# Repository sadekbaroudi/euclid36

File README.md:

# Support me!

I have spent a lot of time and money designing prototypes, testing, developing, etc. Any contributions would be greatly appreciated!

If you don't want to, or can't afford to support me, please send me a message to let me know you've built one, along with pictures. Also, feel free to submit a pull request with pictures into this repository. I'd be happy to showcase your build.

Reddit: /u/sadekbaroudi
Discord: sadekbaroudi#1258

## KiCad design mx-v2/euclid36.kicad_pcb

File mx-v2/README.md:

# euclid36

## The euclid36 supports the following:
* 36 keys
* Two rotary encoders
* 10 bottom facing LEDs for underglow
* 3 top facing LEDs for illumination in the center of the board
* Horizontal OLED near the top of the board
* 3 different types of Joysticks for mouse control
	* PS2/PS3/PS4 type joystick with click button (center of the board)
		* https://www.adafruit.com/product/512
	* 2 axis thumbstick
		* https://www.adafruit.com/product/2765
	* PSP type thumbstick
		* https://www.adafruit.com/product/444
	
### Placement of features:

### Print this file to test the layout. It is to scale

### 3d render

### Layout

_At the time of creation, using Kicad 5.1.9 - This may not work with future versions_

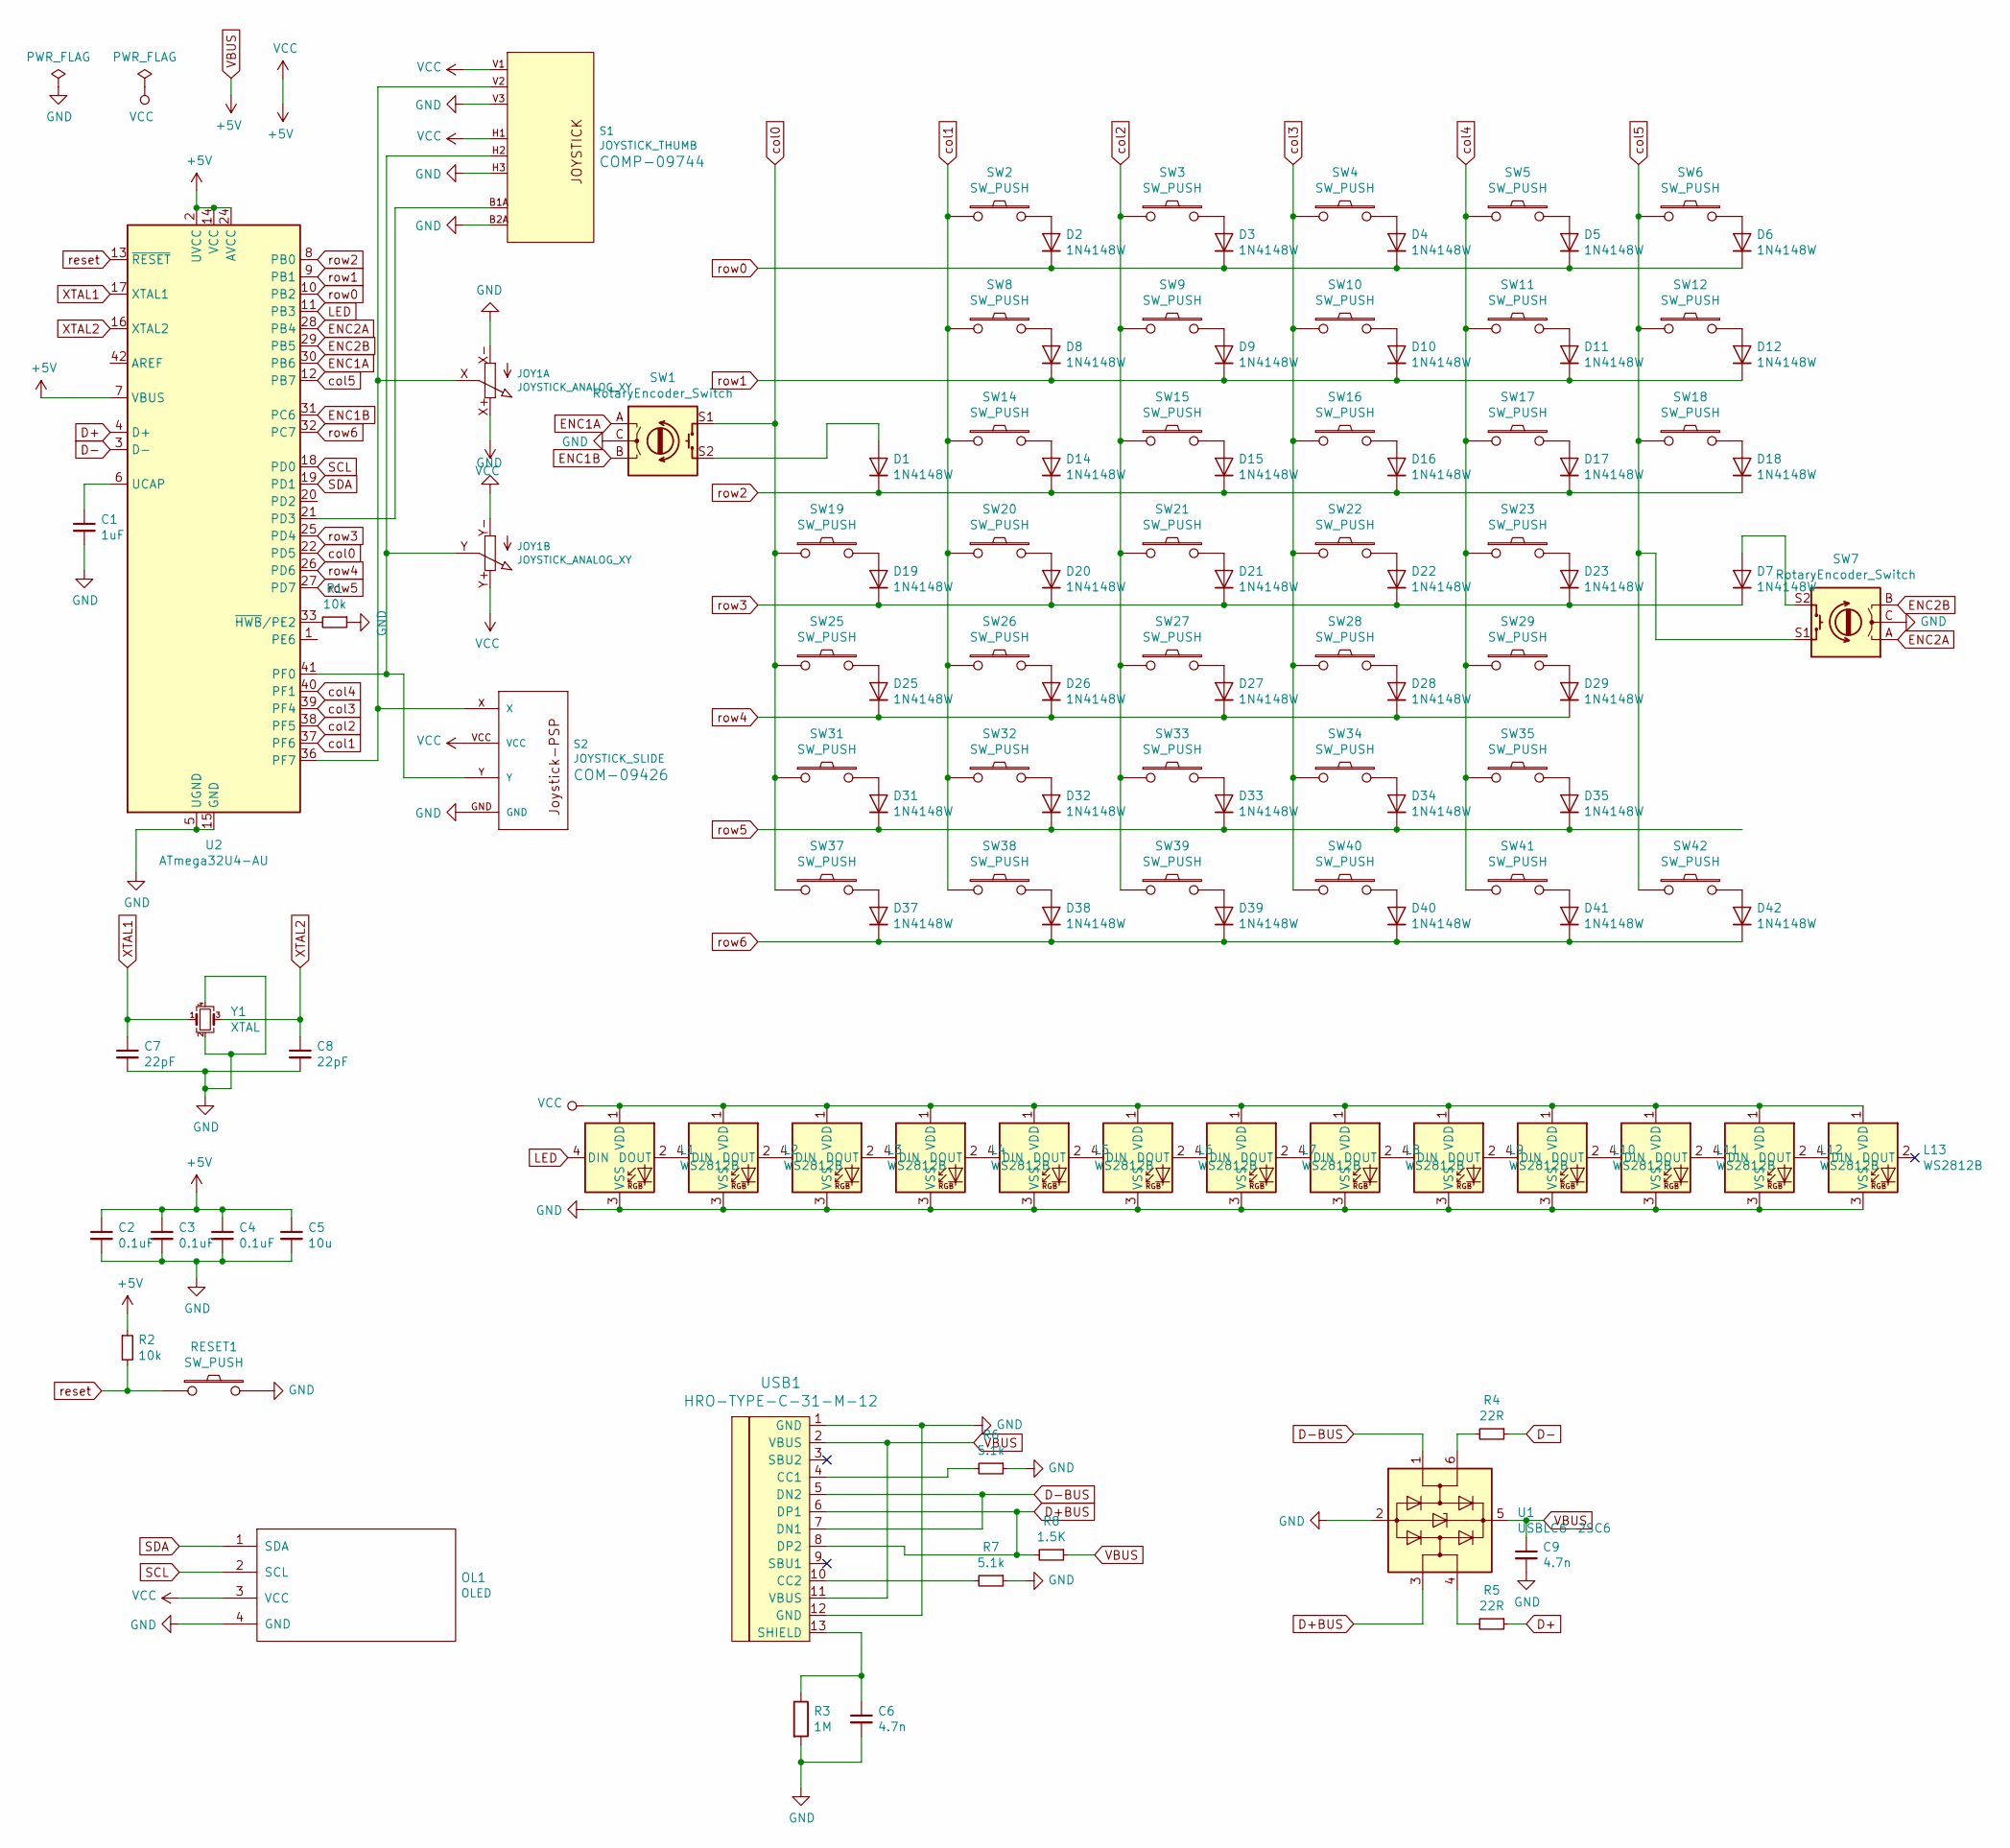
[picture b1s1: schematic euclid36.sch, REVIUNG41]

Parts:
C1: 1uF; C_0805_2012Metric_Pad1.18x1.45mm_HandSolder; LCSC C28323
C2, C3, C4: 0.1uF; C_0805_2012Metric_Pad1.18x1.45mm_HandSolder; LCSC C49678
C5: 10u; C_0805_2012Metric_Pad1.18x1.45mm_HandSolder; LCSC C15850
C6: 4.7n; C_0805_2012Metric; LCSC C50131
C7, C8: 22pF; C_0805_2012Metric_Pad1.18x1.45mm_HandSolder; LCSC C1804
C9: 4.7n; C_0805_2012Metric; LCSC C1744
D1, D2, D3, D4, D5, D6, D7, D8, D9, D10, D11, D12, D14, D15, D16, D17, D18, D19, D20, D21, D22, D23, D26, D27, D28, D29, D31, D32, D33, D34, D35, D37, D38, D39, D40, D41, D42: 1N4148W; D_SOD-123; LCSC C727110
D25: 1N4148W; D_SOD-123; LCSC C81598
JOY1: JOYSTICK_ANALOG_XY; JOYSTICK_ANALOG_MINITHM
L1, L2, L3, L4, L5, L6, L7, L8, L9, L10, L11, L12, L13: WS2812B; LED_WS2812B_PLCC4_5.0x5.0mm_P3.2mm; LCSC C114586
OL1: OLED; OLED_v2
R1, R2: 10k; R_0805_2012Metric; LCSC C17414
R3: 1M; R_0805_2012Metric; LCSC C17514
R4, R5: 22R; R_0805_2012Metric; LCSC C17561
R6, R7: 5.1k; R_0805_2012Metric; LCSC C27834
R8: 1.5K; R_0805_2012Metric; LCSC C4310
RESET1: SW_PUSH; ResetSW_1side
S1: JOYSTICK_THUMB; JOYSTICK
S2: JOYSTICK_SLIDE; JOYSTICK-PSP1000
SW1, SW7: RotaryEncoder_Switch; RotaryEncoder_EC11; LCSC C470750
SW2, SW3, SW4, SW5, SW6, SW8, SW9, SW10, SW11, SW12, SW14, SW15, SW16, SW17, SW18, SW19, SW20, SW21, SW22, SW23, SW25, SW26, SW27, SW28, SW29, SW31, SW32, SW33, SW34, SW35, SW37, SW38, SW39, SW40, SW41, SW42: SW_PUSH; MXOnly-1U-Hotswap
U1: USBLC6-2SC6; SOT-23-6; LCSC C558442
U2: ATmega32U4-AU; ATMEGA32U4-AU; LCSC C44854
USB1: HRO-TYPE-C-31-M-12; HRO-TYPE-C-31-M-12-Assembly; LCSC C165948
Y1: XTAL; Crystal_SMD_3225-4Pin_3.2x2.5mm; LCSC C13738

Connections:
D+: R5.1, U2.4 (D+)
D+BUS: R8.2, U1.3 (I/O2), USB1.6 (DP1), USB1.8 (DP2)
D-: R4.1, U2.3 (D-)
D-BUS: U1.1 (I/O1), USB1.5 (DN2), USB1.7 (DN1)
ENC1A: SW1.A, U2.30 (PB6)
ENC1B: SW1.B, U2.31 (PC6)
ENC2A: SW7.A, U2.28 (PB4)
ENC2B: SW7.B, U2.29 (PB5)
GND: C1.2, C2.2, C3.2, C4.2, C5.2, C6.2, C7.2, C8.2, C9.2, JOY1.X- (A), JOY1.Y- (A), L1.3 (VSS), L2.3 (VSS), L3.3 (VSS), L4.3 (VSS), L5.3 (VSS), L6.3 (VSS), L7.3 (VSS), L8.3 (VSS), L9.3 (VSS), L10.3 (VSS), L11.3 (VSS), L12.3 (VSS), L13.3 (VSS), OL1.4 (GND), R1.1, R3.2, R6.1, R7.1, RESET1.2, S1.B2A (SEL-), S1.H3 (H-), S1.V3 (V-), S2.GND, SW1.C, SW7.C, U1.2 (GND), U2.5 (UGND), U2.15 (GND), U2.23 (GND), U2.35 (GND), U2.43 (GND), USB1.1 (GND), USB1.12 (GND), Y1.2, Y1.4
LED: L1.4 (DIN), U2.11 (PB3)
unnamed: C1.1, U2.6 (UCAP)
unnamed: C6.1, R3.1, USB1.13 (SHIELD)
unnamed: D1.2 (A), SW1.S2
unnamed: D2.2 (A), SW2.2
unnamed: D3.2 (A), SW3.2
unnamed: D4.2 (A), SW4.2
unnamed: D5.2 (A), SW5.2
unnamed: D6.2 (A), SW6.2
unnamed: D7.2 (A), SW7.S2
unnamed: D8.2 (A), SW8.2
unnamed: D9.2 (A), SW9.2
unnamed: D10.2 (A), SW10.2
unnamed: D11.2 (A), SW11.2
unnamed: D12.2 (A), SW12.2
unnamed: D14.2 (A), SW14.2
unnamed: D15.2 (A), SW15.2
unnamed: D16.2 (A), SW16.2
unnamed: D17.2 (A), SW17.2
unnamed: D18.2 (A), SW18.2
unnamed: D19.2 (A), SW19.2
unnamed: D20.2 (A), SW20.2
unnamed: D21.2 (A), SW21.2
unnamed: D22.2 (A), SW22.2
unnamed: D23.2 (A), SW23.2
unnamed: D25.2 (A), SW25.2
unnamed: D26.2 (A), SW26.2
unnamed: D27.2 (A), SW27.2
unnamed: D28.2 (A), SW28.2
unnamed: D29.2 (A), SW29.2
unnamed: D31.2 (A), SW31.2
unnamed: D32.2 (A), SW32.2
unnamed: D33.2 (A), SW33.2
unnamed: D34.2 (A), SW34.2
unnamed: D35.2 (A), SW35.2
unnamed: D37.2 (A), SW37.2
unnamed: D38.2 (A), SW38.2
unnamed: D39.2 (A), SW39.2
unnamed: D40.2 (A), SW40.2
unnamed: D41.2 (A), SW41.2
unnamed: D42.2 (A), SW42.2
unnamed: JOY1.X (S), S1.V2 (V), S2.X, U2.36 (PF7)
unnamed: JOY1.Y (S), S1.H2 (H), S2.Y, U2.41 (PF0)
unnamed: L1.2 (DOUT), L2.4 (DIN)
unnamed: L2.2 (DOUT), L3.4 (DIN)
unnamed: L3.2 (DOUT), L4.4 (DIN)
unnamed: L4.2 (DOUT), L5.4 (DIN)
unnamed: L5.2 (DOUT), L6.4 (DIN)
unnamed: L6.2 (DOUT), L7.4 (DIN)
unnamed: L7.2 (DOUT), L8.4 (DIN)
unnamed: L8.2 (DOUT), L9.4 (DIN)
unnamed: L10.2 (DOUT), L11.4 (DIN)
unnamed: L9.2 (DOUT), L10.4 (DIN)
unnamed: L11.2 (DOUT), L12.4 (DIN)
unnamed: L12.2 (DOUT), L13.4 (DIN)
unnamed: R1.2, U2.33 (~HWB~/PE2)
unnamed: R4.2, U1.6 (I/O1)
unnamed: R5.2, U1.4 (I/O2)
unnamed: R6.2, USB1.4 (CC1)
unnamed: R7.2, USB1.10 (CC2)
unnamed: S1.B1A (SEL+), U2.21 (PD3)
SCL: OL1.2 (SCL), U2.18 (PD0)
SDA: OL1.1 (SDA), U2.19 (PD1)
VBUS: C2.1, C3.1, C4.1, C5.1, C9.1, JOY1.X+ (E), JOY1.Y+ (E), L1.1 (VDD), L2.1 (VDD), L3.1 (VDD), L4.1 (VDD), L5.1 (VDD), L6.1 (VDD), L7.1 (VDD), L8.1 (VDD), L9.1 (VDD), L10.1 (VDD), L11.1 (VDD), L12.1 (VDD), L13.1 (VDD), OL1.3 (VCC), R2.1, R8.1, S1.H1 (H+), S1.V1 (V+), S2.VCC, U1.5 (VBUS), U2.2 (UVCC), U2.7 (VBUS), U2.14 (VCC), U2.24 (AVCC), U2.34 (VCC), U2.44 (AVCC), USB1.2 (VBUS), USB1.11 (VBUS)
XTAL1: C7.1, U2.17 (XTAL1), Y1.1
XTAL2: C8.1, U2.16 (XTAL2), Y1.3
col0: SW1.S1, SW19.1, SW25.1, SW31.1, SW37.1, U2.22 (PD5)
col1: SW2.1, SW8.1, SW14.1, SW20.1, SW26.1, SW32.1, SW38.1, U2.37 (PF6)
col2: SW3.1, SW9.1, SW15.1, SW21.1, SW27.1, SW33.1, SW39.1, U2.38 (PF5)
col3: SW4.1, SW10.1, SW16.1, SW22.1, SW28.1, SW34.1, SW40.1, U2.39 (PF4)
col4: SW5.1, SW11.1, SW17.1, SW23.1, SW29.1, SW35.1, SW41.1, U2.40 (PF1)
col5: SW6.1, SW7.S1, SW12.1, SW18.1, SW42.1, U2.12 (PB7)
reset: R2.2, RESET1.1, U2.13 (~RESET)
row0: D2.1 (K), D3.1 (K), D4.1 (K), D5.1 (K), D6.1 (K), U2.10 (PB2)
row1: D8.1 (K), D9.1 (K), D10.1 (K), D11.1 (K), D12.1 (K), U2.9 (PB1)
row2: D1.1 (K), D14.1 (K), D15.1 (K), D16.1 (K), D17.1 (K), D18.1 (K), U2.8 (PB0)
row3: D7.1 (K), D19.1 (K), D20.1 (K), D21.1 (K), D22.1 (K), D23.1 (K), U2.25 (PD4)
row4: D25.1 (K), D26.1 (K), D27.1 (K), D28.1 (K), D29.1 (K), U2.26 (PD6)
row5: D31.1 (K), D32.1 (K), D33.1 (K), D34.1 (K), D35.1 (K), U2.27 (PD7)
row6: D37.1 (K), D38.1 (K), D39.1 (K), D40.1 (K), D41.1 (K), D42.1 (K), U2.32 (PC7)

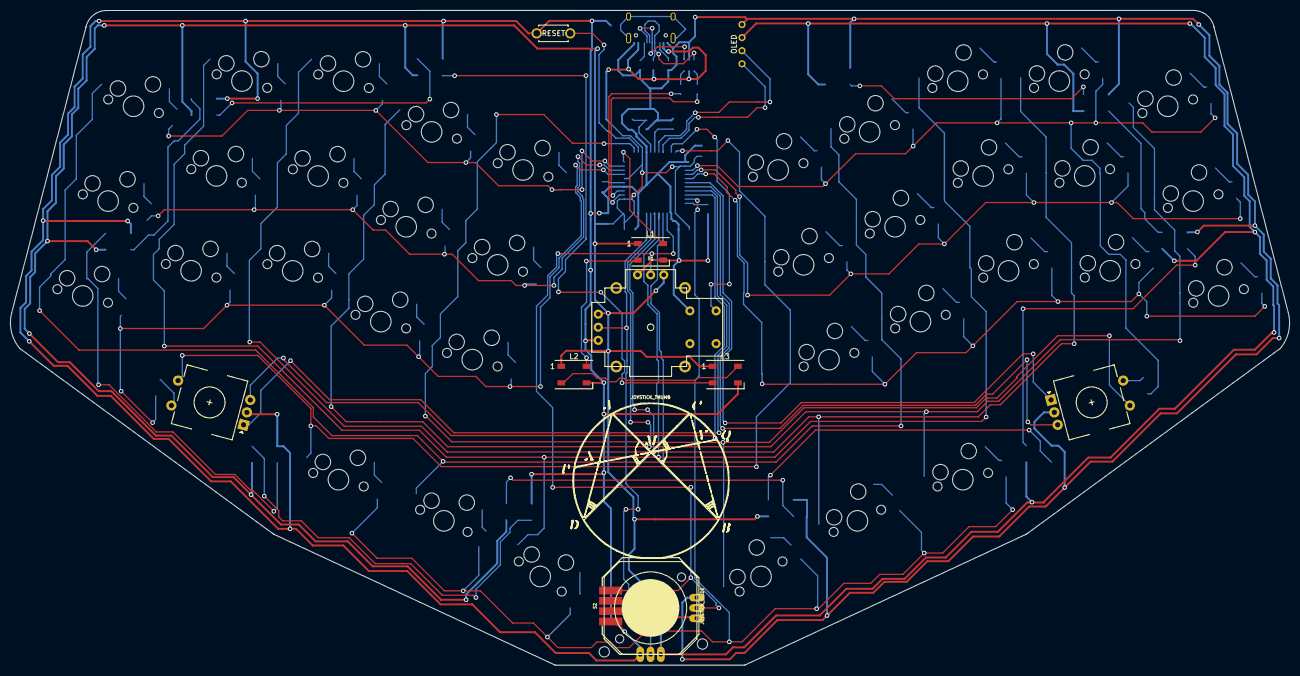
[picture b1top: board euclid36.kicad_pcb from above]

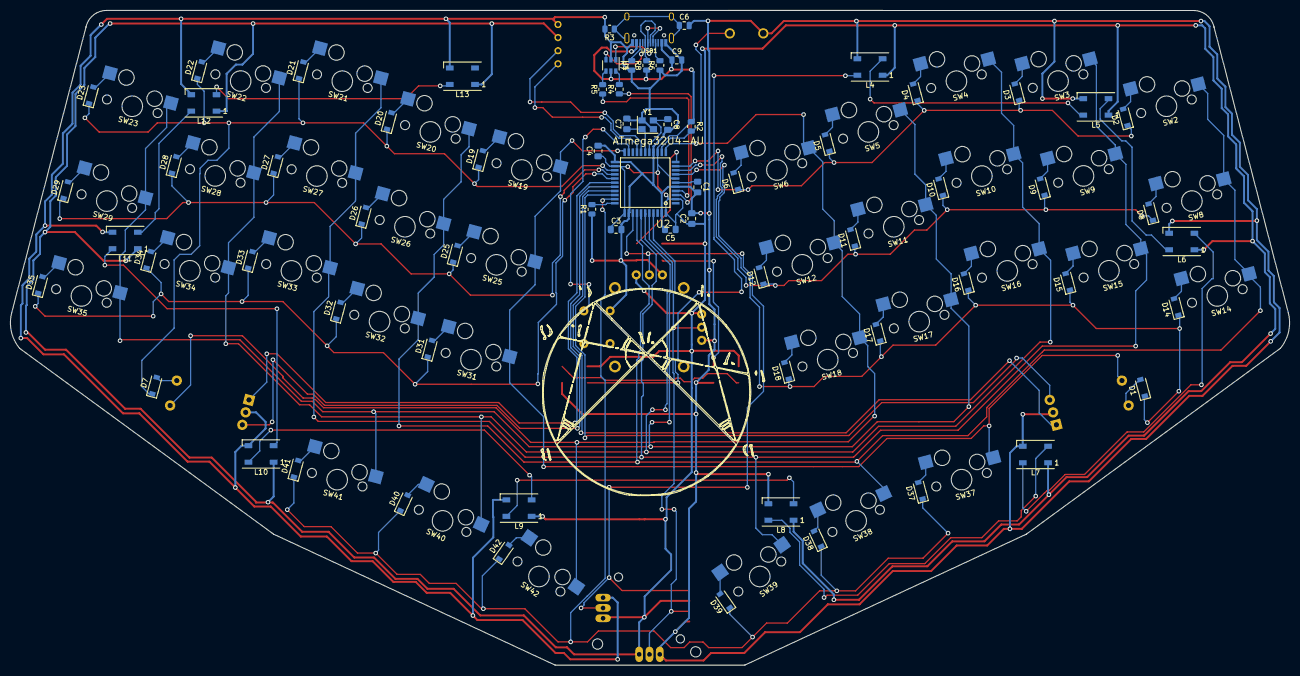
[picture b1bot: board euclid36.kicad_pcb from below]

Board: 2 copper layers, 248.2 x 127.0 mm, 115 parts (69 on the bottom side), 89 nets.

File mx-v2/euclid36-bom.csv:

Comment,Designator,Footprint,LCSC
"1uF","C1","Capacitor_SMD:C_0805_2012Metric_Pad1.18x1.45mm_HandSolder","C28323"
"0.1uF","C2,C3,C4","Capacitor_SMD:C_0805_2012Metric_Pad1.18x1.45mm_HandSolder","C49678"
"10u","C5","Capacitor_SMD:C_0805_2012Metric_Pad1.18x1.45mm_HandSolder","C15850"
"4.7n","C6,C9","Capacitor_SMD:C_0805_2012Metric","C50131"
"22pF","C7,C8","Capacitor_SMD:C_0805_2012Metric_Pad1.18x1.45mm_HandSolder","C1804"
"1N4148W","D1,D2,D3,D4,D5,D6,D7,D8,D9,D10,D11,D12,D14,D15,D16,D17,D18,D19,D20,D21,D22,D23,D25,D26,D27,D28,D29,D31,D32,D33,D34,D35,D37,D38,D39,D40,D41,D42","Diode_SMD:D_SOD-123","C727110"
"JOYSTICK_ANALOG_XY","JOY1","adafruit-analog-thumbstick:JOYSTICK_ANALOG_MINITHM",""
"WS2812B","L1,L2,L3,L4,L5,L6,L7,L8,L9,L10,L11,L12,L13","LED_SMD:LED_WS2812B_PLCC4_5.0x5.0mm_P3.2mm","C114586"
"OLED","OL1","_reviung-kbd:OLED_v2",""
"10k","R1,R2","Resistor_SMD:R_0805_2012Metric","C17414"
"1M","R3","Resistor_SMD:R_0805_2012Metric","C17514"
"22R","R4,R5","Resistor_SMD:R_0805_2012Metric","C17561"
"5.1k","R6,R7","Resistor_SMD:R_0805_2012Metric","C27834"
"1.5K","R8","Resistor_SMD:R_0805_2012Metric","C4310"
"SW_PUSH","RESET1","_reviung-kbd:ResetSW_1side",""
"JOYSTICK_THUMB","S1","SparkFun-Switches:JOYSTICK",""
"JOYSTICK_SLIDE","S2","SparkFun-Switches:JOYSTICK-PSP1000",""
"RotaryEncoder_Switch","SW1,SW7","_reviung-kbd:RotaryEncoder_EC11","C470750"
"SW_PUSH","SW2,SW3,SW4,SW5,SW6,SW8,SW9,SW10,SW11,SW12,SW14,SW15,SW16,SW17,SW18,SW19,SW20,SW21,SW22,SW23,SW25,SW26,SW27,SW28,SW29,SW31,SW32,SW33,SW34,SW35,SW37,SW38,SW39,SW40,SW41,SW42","_reviung-kbd:MXOnly-1U-Hotswap",""
"USBLC6-2SC6","U1","Package_TO_SOT_SMD:SOT-23-6","C558442"
"ATmega32U4-AU","U2","_reviung-kbd:ATMEGA32U4-AU","C44854"
"HRO-TYPE-C-31-M-12","USB1","_reviung-kbd:HRO-TYPE-C-31-M-12-Assembly","C165948"
"XTAL","Y1","Crystal:Crystal_SMD_3225-4Pin_3.2x2.5mm","C13738"

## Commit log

2021-03-16 let the chaos begin
2021-03-16 baseline schematic, need to add more switches
2021-03-16 Assigned footprints to schematic symbols
2021-03-17 Added all 36 keys
2021-03-17 Updated key switch and diode labels
2021-03-17 Created and organized layout, WIP
2021-03-17 flipped some of the components, defined copper width for power
2021-03-17 moved into my own dir
2021-03-17 Added my own modified version of reviung41 that is basically what I want
2021-03-17 got rid of a bunch of unnecessary stuff
2021-03-17 moved pcb up one dir
2021-03-17 removed gerber, was from old unmodded keyboard
2021-03-17 updated libraries to relative paths
2021-03-17 Readme with kicad version
2021-03-17 Moved LEDs closer to bottom edge now that pcb dimensions extended
2021-03-17 Left edge of pcb was a little curved, fixed
2021-03-17 ever so slightly moved the bottom right led down
2021-03-17 flipped the diode from the front to the back and aligned
2021-03-17 removing reviung readme
2021-03-18 Added todo list
2021-03-19 New layout with bigger split, more pinky stagger, and better thumb cluster
2021-03-19 Rev02: Fixed a couple of switch positions and placed all the resistors
2021-03-19 centered some components more precisely
2021-03-20 added edge outline
2021-03-20 First round of working on rounting, wip
2021-03-21 completed all routing, still have unconnected stuff in DRC, need to fix
2021-03-21 Some major changes, replaced diodes with SOD123, fixed some routing, updated footprints to use different libraries
2021-03-22 euclid36 rev, sent to production...
2021-03-23 some cool images of the keyboard
2021-03-23 Removed unnecesary project files and completely renamed to euclid36
2021-03-23 Adding case files
2021-03-23 moved images into subdirectory
2021-03-24 case and plate for euclid36
2021-03-24 Updated case and switch plates
2021-03-24 add latest version of case and switchplate, as well as pcb model
2021-03-25 Images and readme
2021-03-25 wrong image in readme
2021-03-27 new switchplate with legs to support the pressure of keypresses and an svg for laser cutting
2021-03-28 Added drill holes for case standoffs and screws
2021-03-28 removing unneeded files after renaming project
2021-03-30 Added one more hole for another stabilizer in the center
2021-03-30 rev 2 zip file, with bom and cpl, but not sure bom and cpl are valid
2021-03-31 Added smt assembly support for jlcpcb.com, see bom and cpl csvs in gerber zip
2021-03-31 added hole for center standoff
2021-03-31 not really rev 2, renamed
2021-03-31 moved main project into mx folder so I can create new versions of the keyboard in seperate folders
2021-03-31 I broke the readme with the last commit
2021-04-01 adding a new pcb design that is made for kailh choc switches, wip
2021-04-02 Wired everything. Not too happy with it, but I think it works
2021-04-02 Small fixes
2021-04-06 Newest case to use without screws or standoffs, next comes pcb stand for this design
2021-04-07 new cases and pcb support
2021-04-07 more cases
2021-04-07 moved 2 LEDs slightly up as they were overlapping with hotswap sockets
2021-04-08 working prototype README update
2021-04-08 case updates
2021-04-10 Added some items to the library
2021-04-10 complete, ready for fabrication, though might change mini usb to micro usb before doing so
2021-04-12 Updated choc version to use usb-c. Almost done, still need to create a case / svgs
2021-04-12 Updated to include mounting holes and gerber update
2021-04-12 acrylic case support
2021-04-12 Added README with interest check link
2021-04-15 sandwich case
2021-04-15 Readme for sandwich case in the wrong spot
2021-04-21 added mx sandwich case and updated pcb to support OLED
2021-04-22 v2 of euclid36 with integrated MCU, rotary encoders, and OLED
2021-04-22 updated with logo
2021-04-22 updated with drill holes for spacers
2021-04-22 Added one more spacer hole for top and bottom plates
2021-04-23 added printable logo
2021-04-27 Added support for two joysticks, but can't use both at the same time, as they share pins
2021-04-27 whoops, ran drc and had to fix a few things
2021-04-28 latest mx-v2, not sure what I changed
2021-04-28 latest low pro choc keyboard
2021-04-28 accidentally wired my analog joysticks to digital inputs
2021-04-28 typing test video of the MX prototype
2021-05-05 added support for another joystick type, psp, as well as readme update with new feature layout image
2021-05-06 Proto V2 complete and ordered from jlcpcb.com
2021-05-15 adding todo file to track what I still need to do before the next rev
2021-06-17 last revision had a few problems, fixed some, see todo.txt
2021-09-01 added paypal donation link
2021-09-03 added verbiage to ask people to share builds and pictures with me
2021-11-30 updated paypal link to direct paypal instead of donation, since they take 29%
